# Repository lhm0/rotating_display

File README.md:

# Rotating Display

## Abstract: 
 The Rotating Display is a compact disc-sized device that rotates quietly using a CD motor. It features 40 LEDs that display time and weather data sourced from the internet. The device is wirelessly powered and controlled via a user-friendly web interface. It uses Arduino nano and ESP-01s microcontrollers and is easy to assemble.

<p align="center"> 

</p> 

<p align="center"> 

</p> 

## 1. Description of the device

The Rotating Display device comprises two primary units: a power supply unit and a display board (**figure 1**). Both are circular in design, with a diameter of 120mm, similar to the dimensions of a standard Compact Disk. The display board is rotated by a CD motor. Energy is wirelessly transmitted from the power supply unit to the display board, eliminating the need for wired connections.

**Figure 1:  Rotating Display assembly.** The lower PCB is the power supply with wireless power transmission, the upper PCB is the display board.

The display board is equipped with two rows of LEDs, each containing 20 LEDs. This makes a total of 40 LEDs available for image representation. The LED operations are controlled by an Arduino Nano, while an ESP-01s microcontroller generates the display content. The ESP-01s maintains a Wi-Fi connection to the internet for this purpose.

This internet connection allows the device to retrieve the time from a time server, ensuring time accuracy. It also allows for the acquisition of weather data. Device operation is managed through a web interface (**figure 2**), accessible from any web browser. The interface allows users to manage login credentials, upload image files to the display, and control image and configuration files through a file manager.

**Figure 2:** The **web user interface** allows for operating mode selection and device configuration.

## 2. Operating modes

When switched on, the device tries to connect to a known wifi. If no valid wifi credentials are found, the unit will be configured as wifi access point. In this mode, a computer or mobile device can be connected, directly (SSID: RD40, no password). 

Once the wifi connection has been established, the unit will display its IP address on the  home page of the device (**figure 3**). Enter this address in your web browser. This will load the web user interface and will allow you to configure your local wifi.

**Figure 3: home page.**

There are several operating modes that display time and weather information (**figure 4**). The logo clock mode integrates a customizable image into the clock face. The image can be easily uploaded from the user interface. The same is true for the analog clock, which uses a customizable clock face in the background.

**Figure 4: operating modes.** Modes can be selected and configured through the web interface.

## 3. Mechanical design

The device consists of two assemblies: power supply and display. The power supply board is also the base plate, which can either be placed on a flat surface or hung on a wall. A standard CD motor is inserted through a recess in this board so that the CD tray above the board can accommodate the display assembly. The display board is fixed with two M2 screws. Furthermore, the base plate carries a potentiometer to control the motor speed as well as an on/off switch for the motor.

**Figure 5: Power Supply Board** with CD motor (middle), 12V power jack (lower side), and speed potentiometer

An important requirement for the display board is that the center of mass of the unit is exactly in the middle, on the axis of rotation of the motor. This is the only way to ensure smooth and vibration-free running of the display. To achieve this, the electronic components are arranged as symmetrically as possible to the vertical axis of symmetry in **figure 7**. This initially ensures that the center of gravity lies on this vertical axis. However, since the components cannot be distributed symmetrically to the horizontal axis of symmetry, the center of gravity must be shifted to the center along this axis using balancing weights. For this purpose, two M2x6mm screws with two nuts each are placed to the right and left of the Arduino nano. The balancing result is very good, but can certainly be further optimized.

**Figure 6: Display Board.** Main components are the two LED rows, five serial shift register chips, and two microcontrollers (Arduino nano and ESP-01s). On the backside of the board the secondary coil of the wireless power supply is attached.

**Figure 7:** The components of the display board are arranged symmetrically to the vertical axis of symmetry. Therefore, the center of gravity is located on this axis. The vertical position of the center of gravity is adjusted to the middle by means of adjustment weights.

The two LED rows each consist of 20 discrete, rectangular LEDs. The components each have a width of 2mm and can be lined up without spacing. However, the light emitting surface of the LEDs has a diameter of only about 1mm. Thus, there is a 1mm gap between the light points. To fill these gaps, the second row of LEDs is used. It is inclined by 90 degrees along the angle of rotation. Radially, the two LED rows are shifted by 1 mm, creating a dot pattern without gaps (**figure 8**).

**Figure 8:** The two LED rows are displaced radially by half a LED width

The LEDs must output the image information at exactly the right position with each rotation. For spatial alignment of the image, a trigger signal is generated at a defined position for each rotation, which triggers the sequential, clocked output of the pixels. The trigger signal must be spatially very stable, otherwise no smooth image can be generated. It turned out that a Hall sensor is best suited for this purpose. It is located underneath the Arduino nano (see **figure 6**, right picture, bottom edge of the PCB). The magnet is glued into a hole of the power supply PCB (see figure 5, left picture, 4 o'clock position).

## 4. Electronics architecture

The distribution of the electronic circuitry between the two assemblies is shown in **figure 9**. The power supply assembly contains a Royer converter for wireless power transfer to the display assembly and an adjustment of the motor speed. The 40 LEDs of the display assembly are controlled by 5 shift registers (8 bits each), which in turn are supplied with clock and data by an Arduino nano via an SPI interface. The displayed content is generated by an ESP-01s microcontroller, which is connected to the internet via Wifi. It transmits its data to the Arduino nano via an I2C interface.

**Figure 9: electronics schematics.**

## 5. Power supply board

The core of the power supply is a Royer converter for wireless power transfer. An excellent article on the operation and design of the circuit can be found at Mikrocontroller.net (German) and the circuit was taken from there. Two transistors are alternately switched (push pull operation) so that a current flows through one half of the coil at a time. The coil belongs to a resonant circuit with a resonant frequency of about 120 kHz. The control voltage for the transistors is obtained via a coupling coil (**figure 10**). The secondary coil is located below the display board (see **figure 6**, right).

The Royer circuit uses very few components. However, the coil is quite complex. It is a bifilar coil, where the two halves are interleaved. In addition, the coupling coil must be connected with the correct polarity, otherwise the two transistors will be destroyed. In the early stages of development, the coil was wound with copper wire. However, this solution was quite difficult to reproduce, so in the final design the coils (bifilar primary coil, coupling coil, secondary coil) were implemented as a printed circuit (see **figure 5**, left and **figure 6** right). The circuit was found to have surprisingly high and perfectly adequate transmission efficiency, although the quality factor of the printed coils is inevitably compromised. The Royer converter with the printed coil assembly is absolutely safe to rebuild.

**Figure 10: Royer converter**. Compare Mikrocontroller.net for reference.

There is also a circuit for supplying the CD motor on the power supply board (**figure 11**). An LM317 voltage regulator is used to generate a variable voltage between 1.7V and 6.0V, which can be adjusted via a potentiometer. The voltage range corresponds to the specified operating range of the CD motor. The supply of the motor can be interrupted with a switch, for example to allow programming of the microcontrollers.

**Figure 11: variable voltage regulator** for driving the CD motor

## 6. Display Board

**a) The LEDs**

The 40 LEDs of the display board are driven by 5 cascaded 8-bit shift registers (**figure 12**). The registers load the serial data stream of the SPI interface of the Arduino nano, synchronized with the SPI clock (SRCK), and switch the parallel pattern to the LEDs when a rising edge is sent to the register clock (RCK). The TIPC6C595 shift register has open drain DMOS outputs. The LED current is set to 20mA each. The maximum current per register is therefore 160mA, which is well within specification. The brightness of the LEDs can be controlled by their duty cycle. The output enable input (G) of the register is used for this purpose. Only when this input is low, the DMOS outputs of the register are active.

The SPI interface is operated with a clock rate of 16 MHz. The 40 bits are therefore transferred in 40 x 1/16MHz = 2.5µs. Assuming a maximum rotation speed of the display of 2000 RPM, this corresponds to 30ms per revolution. At one full rotation of the display 240 pixels are output per LED. This corresponds to 125µs per pixel. Thus, the transmission time via the SPI bus (2.5µs) is significantly shorter than the display time per pixel.

**Figure 12: circuit diagram of the display board**. Diagram also available as download and on Github.

**b) Arduino interrupts and timing**

The idea of using two microcontrollers (Arduino nano and ESP-01s) is essentially to separate the very time-critical timing of the LED control from the computationally intensive and asynchronous image generation and internet communication. In this way, the Arduino is relieved to the maximum and the display of the image is extremely stable.

The software of the Arduino programmed in C consists of two short interrupt routines. The first routine (INT0) is triggered by the Hall sensor exactly once for each full rotation (**figure 13**). This routine starts timer 1, which sets the duration for which a single row of pixels is displayed. Once the timer expires, it is automatically restarted and a second interrupt routine is triggered (INT1). In this second routine the bit pattern of the LEDs is updated. So in this way a new LED pattern appears with each expiration of timer 1. It is important that timer 1 restarts automatically (hardware controlled). Otherwise there could be a delay if the processor cannot start the interrupt routine immediately (because another routine prevents this, for example).

Another important function is to set the duration of timer 1 so that exactly 240 pixel rows per turn are output. For this purpose, the variable "tpt" (time per turn) is increased by the set value of timer 1 with each call of INT1. The routine INT0 can read tpt and thus knows the exact time duration for one revolution - even if it consists of more or less than 240 timer 1 cycles. The new time per pixel (tpt/240) is then calculated from this value and timer 1 is set accordingly.

To control the brightness of the LEDs, the threshold function of timer 1 is used: as soon as a programmable threshold is exceeded, an output of the Arduino switches. The signal is used to switch on the LEDs for the selected time. The principle is similar to the well known pulse width modulation. However, the pulses are synchronized with the pixel clock.

**Figure 13: Arduino interrupt timing.** Timer 1 clocks the pixel output and sets the LED brightness.

**c) ESP-01s for Internet communication and image generation**

The microcontroller ESP-01s has a Wifi module for internet communication and just two programmable input/output pins. The module is placed at the edge of the display board, because the interference field of the wireless power supply is lowest there. In previous versions of the board, the module was located in the center of the board, which caused the controller to misbehave in a way that was difficult to interpret, apparently due to an interference from the wireless power supply. This issue is fully resolved in the latest version of the display. 

Although a concern in the beginning of the development, it turned out that the fast rotation of the display does not lead to any noticeable impairment of the Wifi connection.

**d) Programming of the microcontrollers**

The Arduino nano can be programmed via its mini-USB socket. During programming the power supply of the display can be switched off (but does not have to).

Programming the ESP-01 is a bit more complicated, because it does not have an integrated USB level converter. Therefore below the microcontroller there is a 6 pin female connector to which a FT232 level converter can be connected. Note the correct orientation of the FT232! Next to the connector a small picture shows the correct orientation. The microcontoller cannot be powered by the computer during programming. Therefore the power supply of the display must be switched on. Before programming, the jumper must be plugged in position "P". Then the reset button next to the controller is pressed so that it changes to programming mode. Now the upload can be started on the computer. Afterwards the jumper is put back to its original position and the system is restarted.

Please note that the program code and the content of the flash disk (especially the code of the internet pages) have to be loaded separately. A good tutorial on how to load the Flash Disk with Visual Studio Code and platformIO can be found here: randomnerdtutorials.com

# 7. The Software of the ESP-01s

The ESP-01s handles the generation of the image data and its transmission to the Arduino nano (once per second). The displayed information (time and weather data) is retrieved from the Internet. Furthermore, the microcontroller serves as a simple HTML web server that can be accessed by any browser to control the display.

**a) Generation of the image data**

Even though the resolution of the display achieved with the 40 LEDs is relatively low, it is sufficient to display images and text upright, undistorted and therefore easily readable. The image data is generated in a rectangular pixel matrix (i.e. a cartesian coordinate system) with 110 x 110 pixels (**figure 14**). This bitmap then has to be transformed into the polar coordinate system of the rotating LED rows, before it is transferred to the Arduino. To make the transformation fast, a lookup table is used, which transforms the x,y coordinates of the bitmap into the r, theta coordinates of the rotating LED lines. The transformation also takes into account the alternating order of the LEDs between the two rows and the 90 degree angle between the two rows.

**Figure 14:** The display handles a **110x110 pixel bitmap**, which is transformed into the polar coordinate system of the rotating LED rows

**b) Control of the display via web interface**

For the implementation of the web server the library ESPAsyncWebServer is used. It has the advantage that the server activity runs in the background independent of other processes running simultaneously on the controller. The server retrieves the HTML, CSS and JS data of the displayed web pages from the local file system (LittleFS) of the microcontroller. Therefore, the web pages and the server can be implemented independently. Retrieving or modifying data is done using the HTTP GET and POST methods.

Certain parameters (brightness of the LEDs, operating mode of the display) can be set via the web interface. In addition, configuration data, such as the access data to the weather service openweather.org or the Wifi data can be edited and saved. These data are also stored in the file system LittleFS of the ESP-01 and are therefore also available after a reboot.

The LittleFS file system allows files to be organized in a directory structure and stored in the microcontroller's flash disk. The user interface of the device has a file browser with which files can be uploaded from the end device (e.g. mobile device) to the microcontroller or downloaded from the microcontroller. This is especially important to be able to load image data to the device. In addition, files and entire directories can be deleted, renamed and moved. This simplifies the organization of the flash disk considerably.

**c) Software architecture**

The ESP-01 software is written in C++. In order to keep an overview despite the large amount of software, the function blocks and the data have been divided into classes. The following is a brief description of the most important classes:

Class RD40

The class provides the central rotating display object. It manages the (private) data of the displayed image (one bit per LED). The class has methods for displaying bitmaps and for passing data to the display controller.

Class myBMP

This class creates 110x110 bit bitmaps for display. It uses private methods to print text on the bitmap, draw lines and circles, or load images.

Class WebInterface

This class manages the web user interface. Once the webInterface object has been initiated, the web server will run in the background without the need for any attention from the software. The class provides certain attributes, such as clockMode and brightness, which are managed by the web interface. The user can change configuration data via the web interface. The data is then stored as parameter files on the flash disk.

Not being a software engineer myself, the source code would most certainly benefit from a code review and revision.

**d) Development Environment**

Visual Studio Code with the PlatformIO extension was used as the development environment. The environment is much faster and more comfortable than the Arduino IDE. In addition, it can also be used for the development of the source code of the web pages.

## 8. Reproduction of the rotating display

All necessary data, such as source code, circuit diagrams, printed board layouts, parts list and sources of supply are included either in this article or in my public github repository. They may be used for non-commercial purposes, such as by hobbyists or in education, whether for reproduction or further development. Either way, please respect the terms of the license.

The device mainly uses standard components that are easy to obtain. The only exceptions could be the LEDs and the shift register (TIPC6C595, Texas Instruments). The LEDs can be purchased from LED1.de (€ 0,32 per piece, from purchase of 50 pieces). The shift register is available in large quantities from DigiKey at the time of writing. The circuit boards were manufactured at Aisler.net.

In the following some hints for the assembly are given. The assembly is simple, especially since almost only through-hole components are used. Nevertheless, good soldering skills are required. As a beginner project the device is only conditionally suitable.

**Figure 15:** Start with the assembly of the power supply board. Insert and solder all electronic components, Afterwards, insert the CD motor from the soldering side and bond it with a fast curing two component epoxy resin.

**Figure 16:** Two M2 nuts are glued into the CD tray PCB. It is attached with double-sided adhesive tape to the back side of the CD motor tray. Two M2 screws may help to bring the PCB into the right position.

**Figure 17:** The rubber bumpers are glued to the ends of the 20 mm long bolts with the epoxy resin. The magnet is then glued into the hole provided for it. Attention: the correct orientation of the magnet (with the right side up) is very important! Make sure that the device works properly before you glue the magnet!

**Figure 18:** Continue with the display board assembly. First prepare the LEDs by shortening the wires. Insert them one row at a time. Hold the LEDs in place with tape before soldering. Note: The LEDs must be inserted in the correct orientation. Use the picture as a reference to identify the cathode and anode of the components. Note the marking on the PCB (A = Anode, K = Cathode).

**Figure 19:** Note: The Hall sensor is the only component, that is inserted through the holes from the soldering side! It must be installed before inserting the Arduino nano, because the Hall sensor is soldered to the component side of the board, underneath the Arduino nano.

**Figure 20:** When all components are installed, the secondary coil PCB can be attached using 4 pins.

## 9. Conclusions

The rotating display works according to a simple principle. However, the development of the Rotating Display device presented numerous highly interesting engineering challenges. Finding solutions for this was not only very interesting, but an opportunity to learn a wide variety of technologies. Last but not least, it was an intellectual challenge that I enjoyed a lot.

Worth mentioning are:

* Simple design with few mechanical components
* Replicable wireless power supply with printed coils
* Alternating arrangement of LEDs to achieve higher resolution
* Complete balancing of the display board to ensure vibration-free operation
* Timer controlled clocking of the LEDs and regulation of their brightness
* User-friendly interface via a standard web browser
* Retrieval of time and weather data from the internet
* Implementation of a file browser for the ESP-01’s flash disk for uploading image data
* Transparent, object-oriented structure of the ESP-01s software

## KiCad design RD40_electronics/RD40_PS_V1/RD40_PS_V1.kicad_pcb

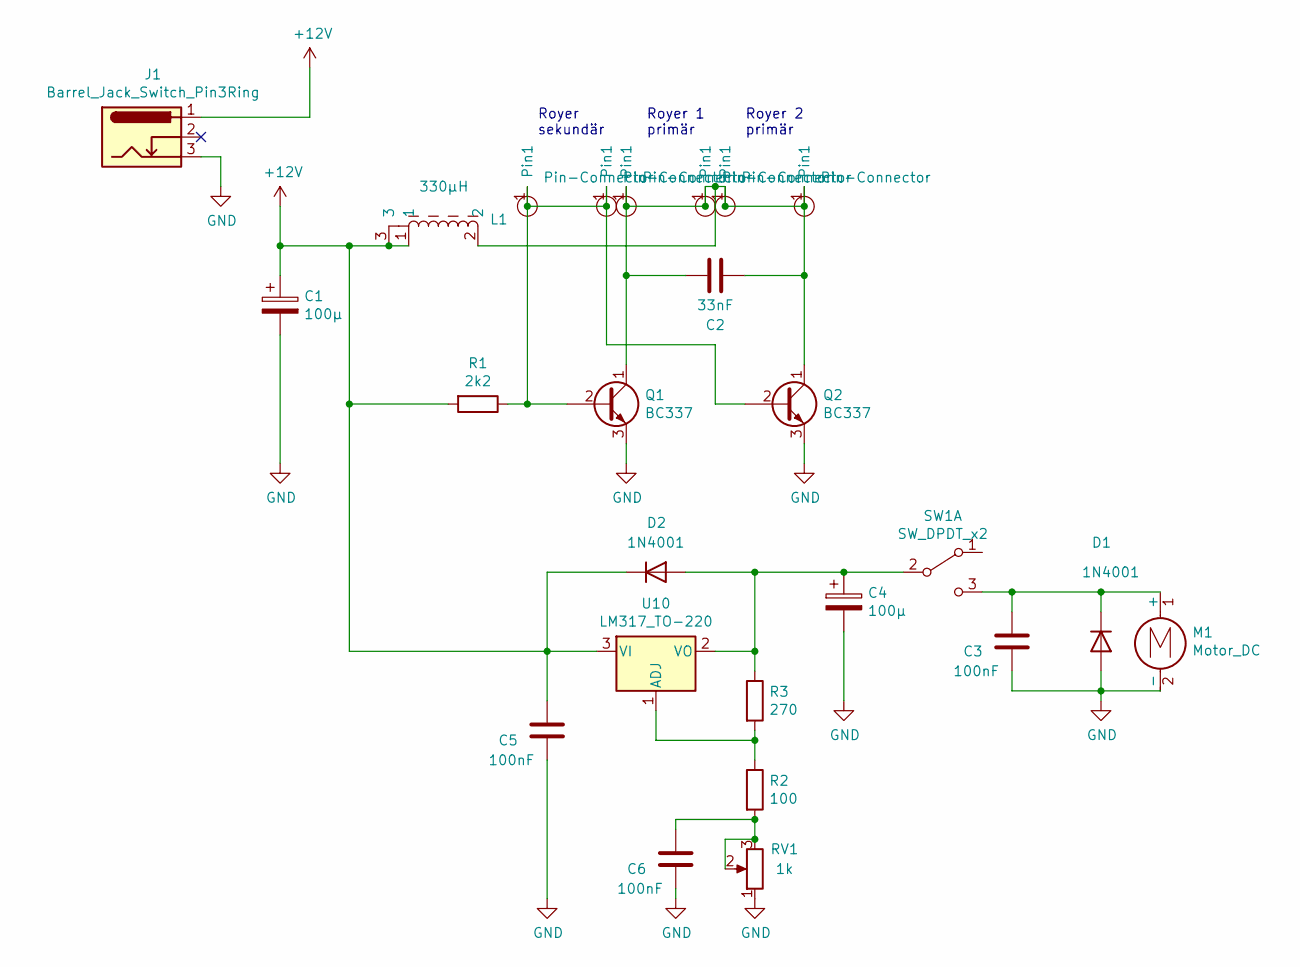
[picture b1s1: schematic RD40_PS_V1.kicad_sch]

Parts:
C1, C4: 100µ; CP_Radial_D6.3mm_P2.50mm
C2: 33nF; MKP10_630V
C3, C5, C6: 100nF; C_Rect_L7.0mm_W2.0mm_P5.00mm
D1, D2: 1N4001; D_DO-41_SOD81_P10.16mm_Horizontal
J1: Barrel_Jack_Switch_Pin3Ring; GRAVITECH_CON-SOCJ-2155
L1: 330µH; L_vertical12
M1: Motor_DC; motor
Q1, Q2: BC337; TO-92_Inline_Wide
R1: 2k2; R_Axial_DIN0207_L6.3mm_D2.5mm_P10.16mm_Horizontal
R2: 100; R_Axial_DIN0207_L6.3mm_D2.5mm_P10.16mm_Horizontal
R3: 270; R_Axial_DIN0207_L6.3mm_D2.5mm_P10.16mm_Horizontal
RV1: 1k; Poti_10mm
SW1: SW_DPDT_x2; Switch1
U1, U2, U3, U4, U5, U6: Pin-Connector; Pin_2mm
U10: LM317_TO-220; TO220_horizontal

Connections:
+12V: C1.1, C5.1, D2.1 (K), J1.1, L1.1, L1.3, R1.2, U10.3 (VI)
GND: C1.2, C3.2, C4.2, C5.2, C6.2, D1.2 (A), J1.3, M1.2 (-), Q1.3 (E), Q2.3 (E), RV1.1
unnamed: C2.1, C2.2, L1.2, Q1.1 (C), Q2.1 (C), U3.1, U4.1, U5.1, U6.1
unnamed: C3.1, D1.1 (K), M1.1 (+), SW1.3 (C)
unnamed: C4.1, D2.2 (A), R3.1, SW1.2 (B), U10.2 (VO)
unnamed: C6.1, R2.2, RV1.2, RV1.3
unnamed: Q1.2 (B), Q2.2 (B), R1.1, U1.1, U2.1
unnamed: R2.1, R3.2, U10.1 (ADJ)

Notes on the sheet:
Royer 2 primär
Royer sekundär
Royer 1 primär

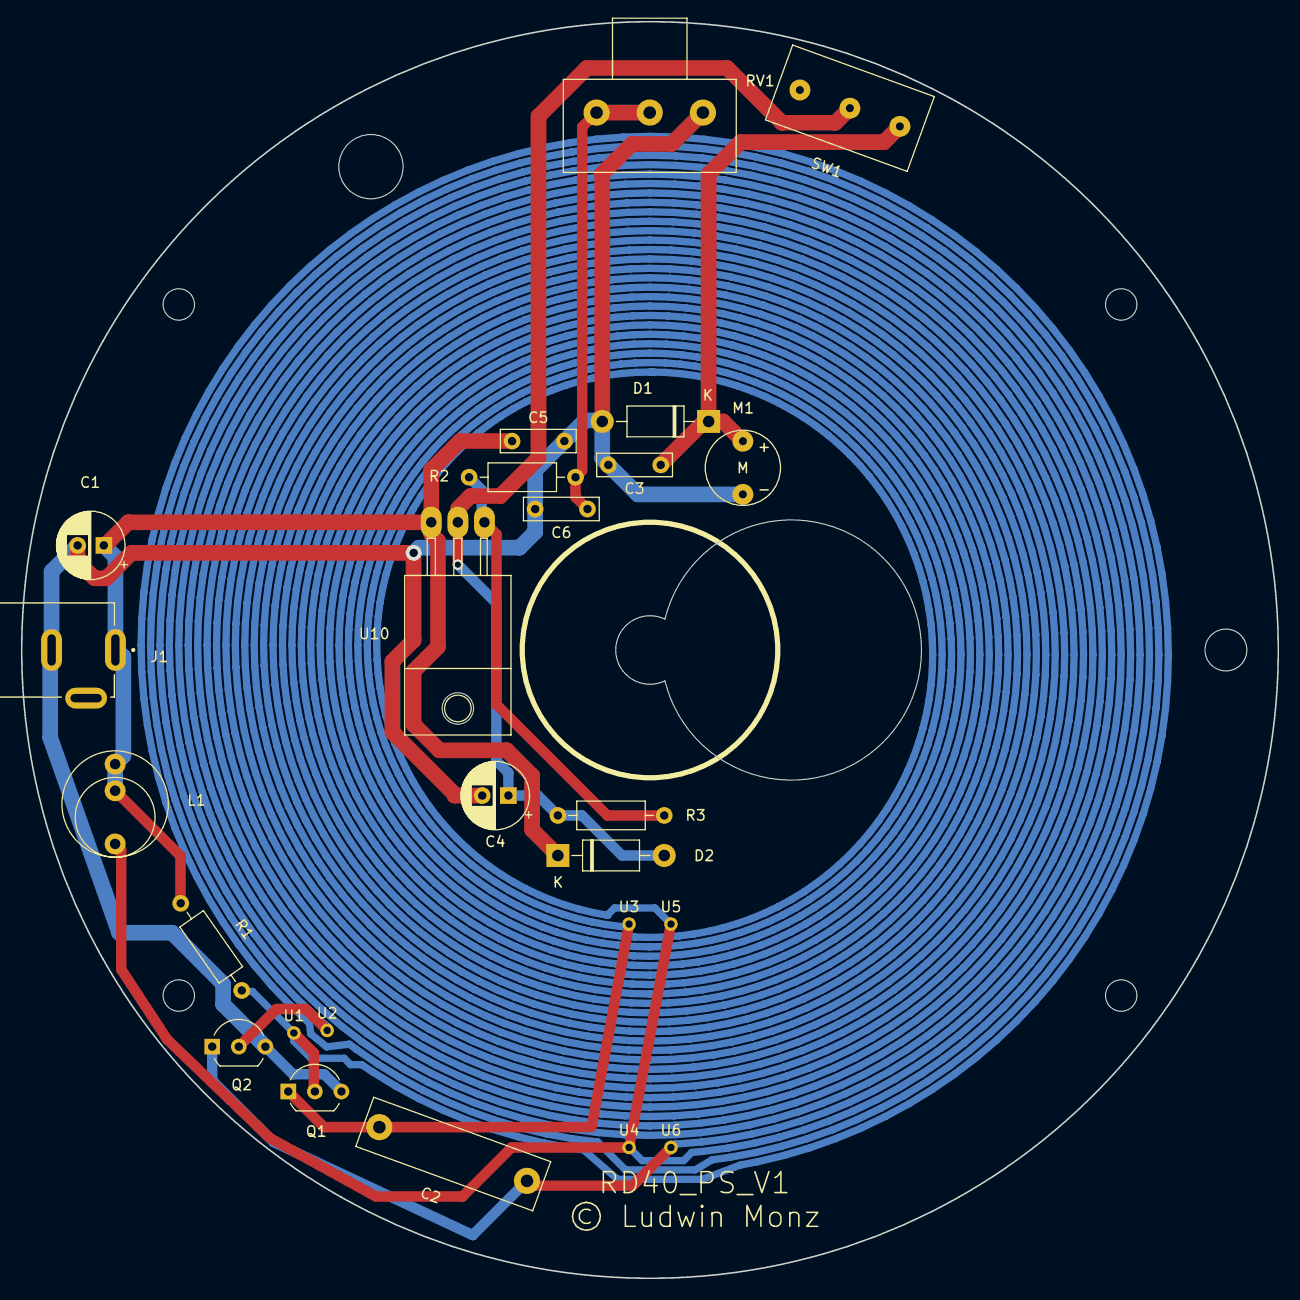
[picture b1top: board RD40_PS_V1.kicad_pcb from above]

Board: 2 copper layers, 120.0 x 120.0 mm, 25 parts (0 on the bottom side), 8 nets.

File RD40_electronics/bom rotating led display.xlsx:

BOM Rotating LED Display
Power Supply Board
item # | Abbrev. | pieces | description | Source | Part Number | link | price | remark
 |  |  |  |  |  |  | PLEASE UPDATE PRICES. THE BELOW IS NOT UP TO DATE. FURTHERMORE, LOW QUANTITY PR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
1 | J1 | 1 | CONN PWR JACK 2.1X5.5MM SOLDER | Digi-Key | EJ503A-ND | https://www.digikey.de/short/d4d54834 | 1.37
2 | U10 | 1 | LM317 | Digi-Key | 2156-LM317LZ/T1-ND | https://www.digikey.de/short/3b2j84zr | 0.23
3 | Q1 | 1 | BC337 | Digi-Key | BC33725TFRCT-ND | https://www.digikey.de/short/9hhf83c4 | 0.35
4 | Q2 | 1 | BC337 | Digi-Key | BC33725TFRCT-ND | https://www.digikey.de/short/9hhf83c4 | 0.35
5 | D1 | 1 | 1N4001 | Digi-Key | 1N4004-T | https://www.digikey.de/short/9qwp2b5q | 0.22
6 | D2 | 1 | 1N4001 | Digi-Key | 1N4004-T | https://www.digikey.de/short/9qwp2b5q | 0.22
7 | R1 | 1 | resistor 4k7 | generic |  |  | 0.1
8 | R2 | 1 | resistor 100 | generic |  |  | 0.1
9 | R3 | 1 | resistor 270 | generic |  |  | 0.1
10 | RV1 | 1 | Potentiometer 1k linear | Digi-Key | P160KN-0QD15B1K | https://www.digikey.de/short/240nt5jz | 0.1
11 | C1 | 1 | capacitor 100uF | Digi-Key | EEU-FM1E101 | https://www.digikey.de/short/ndpjmjr8 | 0.44
12 | C2 | 1 | capacitor 33nF, MKP10, 630V | Reichelt | MKP10-630 33N | https://www.reichelt.de/mkp10-pp-puls-kondensator-33-nf-10-6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 | 0.32 | critical component! do NOT change type!!
13 | C3 | 1 | capacitor ceramic 100nF | generic
14 | C4 | 1 | capacitor 100uF | Digi-Key | EEU-FM1E101 | https://www.digikey.de/short/ndpjmjr8 | 0.26
15 | C5 | 1 | capacitor ceramic 100nF | generic
16 | C6 | 1 | capacitor ceramic 100nF | generic |  |  | 0.44
17 | L1 | 1 | Coil 330 uH | Reichelt | L-09HVP 330µ | https://www.reichelt.de/stehende-induktivitaet-09hvp-ferrit-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 | 0.87
18 | M1 | 1 | CD motor with tray | Amazon, ebay | RF-300F-12350 |  | 3.5
19 | magnet | 1 | magnet, diameter 6mm, thickness 3 mm | Amazon | Multi-Use Neodym Magnete - 6 x 3 mm | https://www.amazon.de/UTOMAG-Multi-Use-Neodym-Magnete-Aufbew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 | 0.18
20 | screw | 2 | M2x6 screw | generic
21 | M2 nuts | 2 | M2 nuts | generic
22 | bolt | 4 | bolt M3x20mm, female - female | Der Schraubenladen | Abstandsbolzen Messing vernickelt | https://shop.der-schraubenladen.de/schrauben/abstandsbolzen/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 | 0.4
23 | screw | 7 | screw flat head, M3x6 | Der Schraubenladen | ISO 7380-2 Linsenschraube mit Flansch Innensechskant Edelstahl A2 | https://shop.der-schraubenladen.de/schrauben/metrische-schra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 | 0.16
24 | bumper | 4 | bumper lens shape, diam. 6.4 mm, thickness 1.9 mm | Amazon | Home Xpert 70 Stück Schutzpuffer CLEAR Linse | https://amzn.eu/d/7VAHGcK | 0.2
25 | PCB | 1 | RD40_PS_V1 | Aisler |  | https://aisler.net/p/ANGDVGXG | 19.16
26 | PCB | 1 | tray | Aisler |  | https://aisler.net/p/DSNBUGJX | 5.21
 |  |  |  |  |  |  | 34.28

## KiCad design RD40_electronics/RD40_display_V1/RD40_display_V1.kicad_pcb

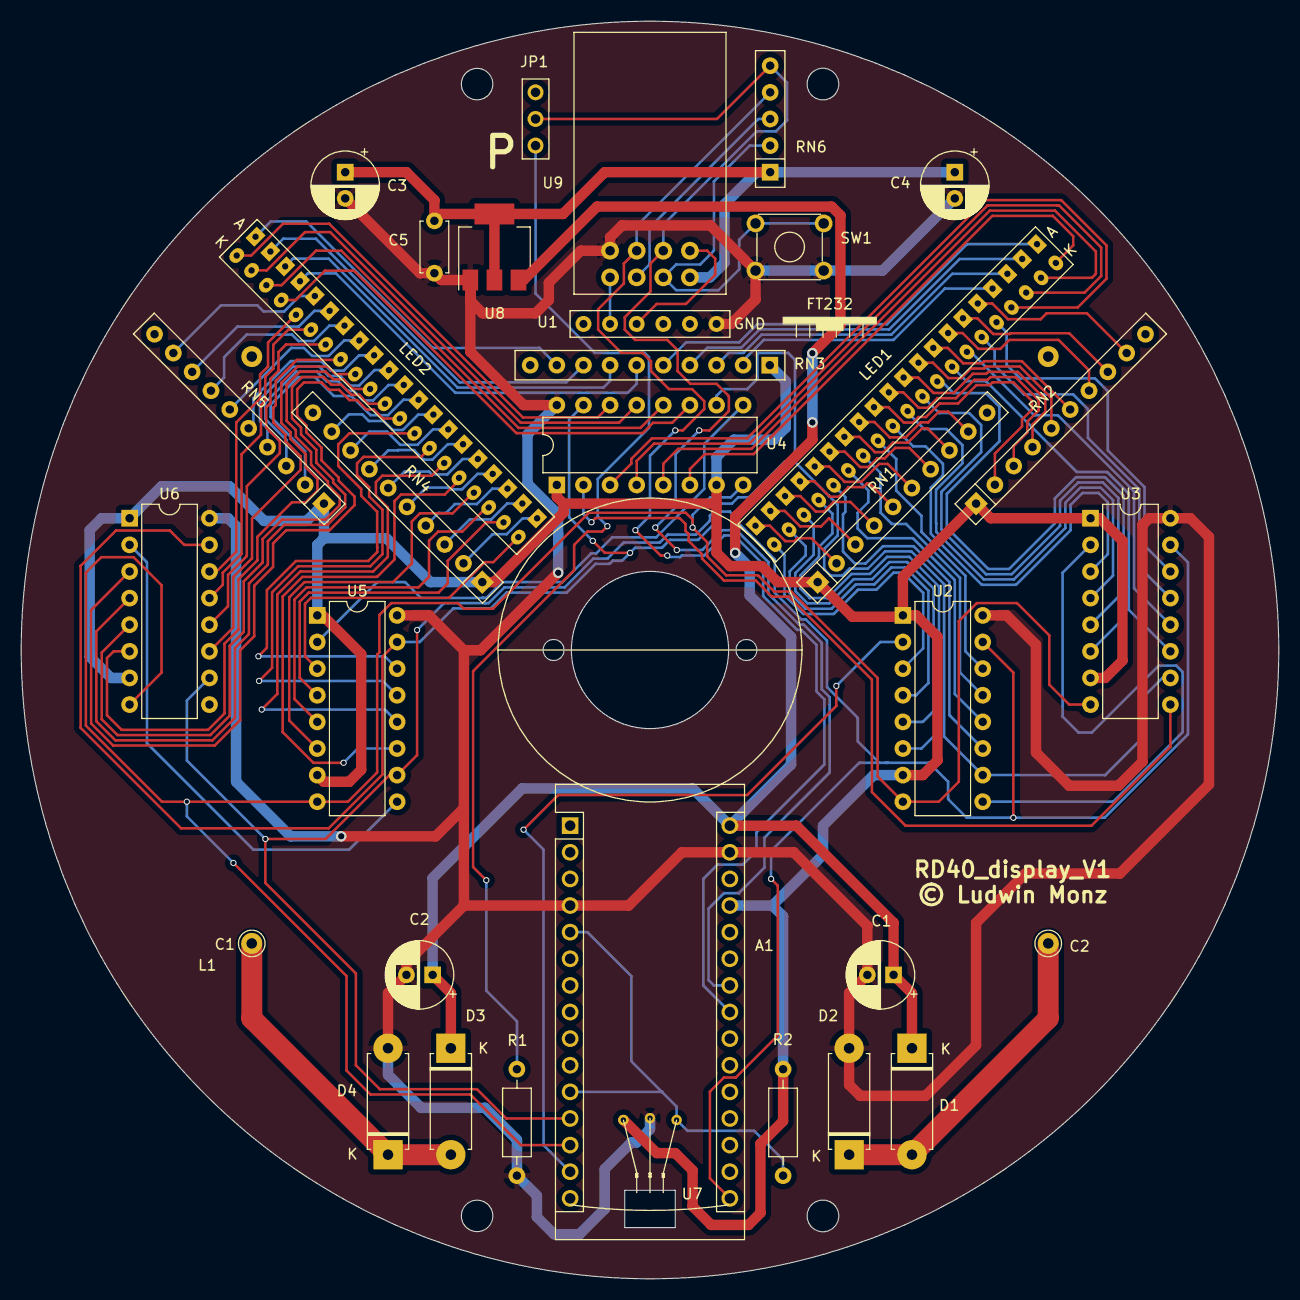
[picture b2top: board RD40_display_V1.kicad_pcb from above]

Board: 2 copper layers, 120.0 x 120.0 mm, 32 parts (0 on the bottom side), 102 nets.

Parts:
A1: Arduino_Nano_v2.x; Arduino_Nano
C1, C2: 220µF; CP_Radial_D6.3mm_P2.50mm
C3, C4: 100µF; CP_Radial_D6.3mm_P2.50mm
C5: 100nF; C_Disc_D4.7mm_W2.5mm_P5.00mm
D1, D2, D3, D4: D_Schottky; D_5W_P10.16mm_Horizontal
JP1: Jumper_3_Open; Jumper_3pin
L1: Coil; coil_large
LED1: LED_line; LED_line_2.0_r
LED2: LED_line; LED_line_2.0_l
R1: 470; R_Axial_DIN0207_L6.3mm_D2.5mm_P10.16mm_Horizontal
R2: 20k; R_Axial_DIN0207_L6.3mm_D2.5mm_P10.16mm_Horizontal
RN1, RN2, RN3, RN4, RN5: 100R; R_Array_SIP10
RN6: 4x10k; R_Array_SIP5
SW1: SW_Push; OmronTaster
U1: FT232
U2, U3, U4, U5, U6: TPIC6C595; DIP-16_W7.62mm
U7: A3144
U8: LM1117-3.3; SOT-223-3_TabPin2
U9: ESP8266_01s

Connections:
GND: A1.4, A1.29, C1.2, C2.2, C3.2, C4.2, C5.2, D2.2, D4.2, R1.2, SW1.2, U1.6, U2.16, U3.16, U4.16, U5.16, U6.16, U7.2, U8.1, U9.4
unnamed: A1.5, A1.11, R2.1, U7.3
unnamed: A1.12, U2.10, U3.10, U4.10, U5.10, U6.10
unnamed: A1.13, U2.8, U3.8, U4.8, U5.8, U6.8
unnamed: A1.14, U2.2
unnamed: A1.16, U2.15, U3.15, U4.15, U5.15, U6.15
unnamed: A1.23, RN6.4, U9.3
unnamed: A1.24, JP1.2, RN6.5, U9.2
unnamed: A1.27, R2.2, RN1.1, RN2.1, RN3.1, RN4.1, RN5.1, U2.1, U2.7, U3.1, U3.7, U4.1, U4.7, U5.1, U5.7, U6.1, U6.7, U7.1
unnamed: A1.30, C1.1, C2.1, D1.1, D3.1, U8.3
unnamed: C3.1, C4.1, C5.1, RN6.1, U8.2, U9.5
unnamed: D1.2, D2.1, L1.2
unnamed: D3.2, D4.1, L1.1
unnamed: JP1.1, R1.1
unnamed: LED1.1, U2.3
unnamed: LED1.2, RN1.2
unnamed: LED1.3, U2.4
unnamed: LED1.4, RN1.3
unnamed: LED1.5, U2.5
unnamed: LED1.6, RN1.4
unnamed: LED1.7, U2.6
unnamed: LED1.8, RN1.5
unnamed: LED1.9, U2.11
unnamed: LED1.10, RN1.6
unnamed: LED1.11, U2.12
unnamed: LED1.12, RN1.7
unnamed: LED1.13, U2.13
unnamed: LED1.14, RN1.8
unnamed: LED1.15, U2.14
unnamed: LED1.16, RN1.9
unnamed: LED1.17, U3.3
unnamed: LED1.18, RN2.2
unnamed: LED1.19, U3.4
unnamed: LED1.20, RN2.3
unnamed: LED1.21, U3.5
unnamed: LED1.22, RN2.4
unnamed: LED1.23, U3.6
unnamed: LED1.24, RN2.5
unnamed: LED1.25, U3.11
unnamed: LED1.26, RN2.6
unnamed: LED1.27, U3.12
unnamed: LED1.28, RN2.7
unnamed: LED1.29, U3.13
unnamed: LED1.30, RN2.8
unnamed: LED1.31, U3.14
unnamed: LED1.32, RN2.9
unnamed: LED1.33, U4.3
unnamed: LED1.34, RN3.2
unnamed: LED1.35, U4.4
unnamed: LED1.36, RN3.3
unnamed: LED1.37, U4.5
unnamed: LED1.38, RN3.4
unnamed: LED1.39, U4.6
unnamed: LED1.40, RN3.5
unnamed: LED2.1, U5.3
unnamed: LED2.2, RN4.2
unnamed: LED2.3, U5.4
unnamed: LED2.4, RN4.3
unnamed: LED2.5, U5.5
unnamed: LED2.6, RN4.4
unnamed: LED2.7, U5.6
unnamed: LED2.8, RN4.5
unnamed: LED2.9, U5.11
unnamed: LED2.10, RN4.6
unnamed: LED2.11, U5.12
unnamed: LED2.12, RN4.7
unnamed: LED2.13, U5.13
unnamed: LED2.14, RN4.8
unnamed: LED2.15, U5.14
unnamed: LED2.16, RN4.9
unnamed: LED2.17, U6.3
unnamed: LED2.18, RN5.2
unnamed: LED2.19, U6.4
unnamed: LED2.20, RN5.3
unnamed: LED2.21, U6.5
unnamed: LED2.22, RN5.4
unnamed: LED2.23, U6.6
unnamed: LED2.24, RN5.5
unnamed: LED2.25, U6.11
unnamed: LED2.26, RN5.6
unnamed: LED2.27, U6.12
unnamed: LED2.28, RN5.7
unnamed: LED2.29, U6.13
unnamed: LED2.30, RN5.8
unnamed: LED2.31, U6.14
unnamed: LED2.32, RN5.9
unnamed: LED2.33, U4.11
unnamed: LED2.34, RN3.6
unnamed: LED2.35, U4.12
unnamed: LED2.36, RN3.7
unnamed: LED2.37, U4.13
unnamed: LED2.38, RN3.8
unnamed: LED2.39, U4.14
unnamed: LED2.40, RN3.9
unnamed: RN6.2, SW1.1, U9.6
unnamed: RN6.3, U9.7
unnamed: U1.2, U9.8
unnamed: U1.3, U9.1
unnamed: U2.9, U3.2
unnamed: U3.9, U4.2
unnamed: U4.9, U5.2
unnamed: U5.9, U6.2

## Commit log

2023-07-12 add images folder
2023-07-13 Create License CC-BY-NC-SA
2023-07-18 add bill of material (BOM)
2023-08-12 apiKey deleted. Obtain own from openweathermap.org
2023-08-16 WORK IN PROGRESS: new SMD display PCB - DO NOT USE
2023-08-17 new feature: time zone selection added
2023-08-17 new feature: time zone selection -> cleanup
2023-08-17 new feature: time zone selection - polished
2023-08-17 sample images added
2023-08-17 sample images - updated
2023-08-20 worked on microcontroller schematics
2023-08-25 SMD circuit diagram further completed
2023-08-30 SMD PCB moved to a separate repository
2023-10-22 fix time zone table
2023-11-01 bug fix config weather
2023-11-02 improve connection with openweathermap
2023-11-03 added serial outputs on weather
2023-11-03 change to weather download
2023-11-03 change GET method for weather request
2025-01-23 minor additions to PCBs
2025-01-28 cleanup of code, new gear animation
2025-01-29 multiple code simplifications and improvements
2025-01-30 new simple software version for RD40
2025-01-30 added reame.txt to RD40_simple
2025-01-31 add "very simple" version for ESP01s
2025-01-31 Simplify print routine
2025-01-31 made print12x18 more robust
2025-02-15 add print10x15() function to RD40_simple_ESP8266
2025-09-16 Remove tracked .DS_Store files and ignore them
2026-02-09 added some photos

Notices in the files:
RD40_electronics/RD40_PS_V1/RD40_PS_V1.kicad_pcb:
© Ludwin Monz
RD40_electronics/RD40_PS_V1/RD40_PS_V1.kicad_sch:
https://creativecommons.org/licenses/by-nc-sa/4.0
License: Creative Commons Attribution-Non-Commercial (CC BY-NC-SA)
